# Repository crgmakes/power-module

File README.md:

# Aquarius Power Module

Main power module for Aquarius

# Software 

You will need [KiCad](https://kicad.org) to view and edit this design. Click [here](https://www.kicad.org/download/) to download.

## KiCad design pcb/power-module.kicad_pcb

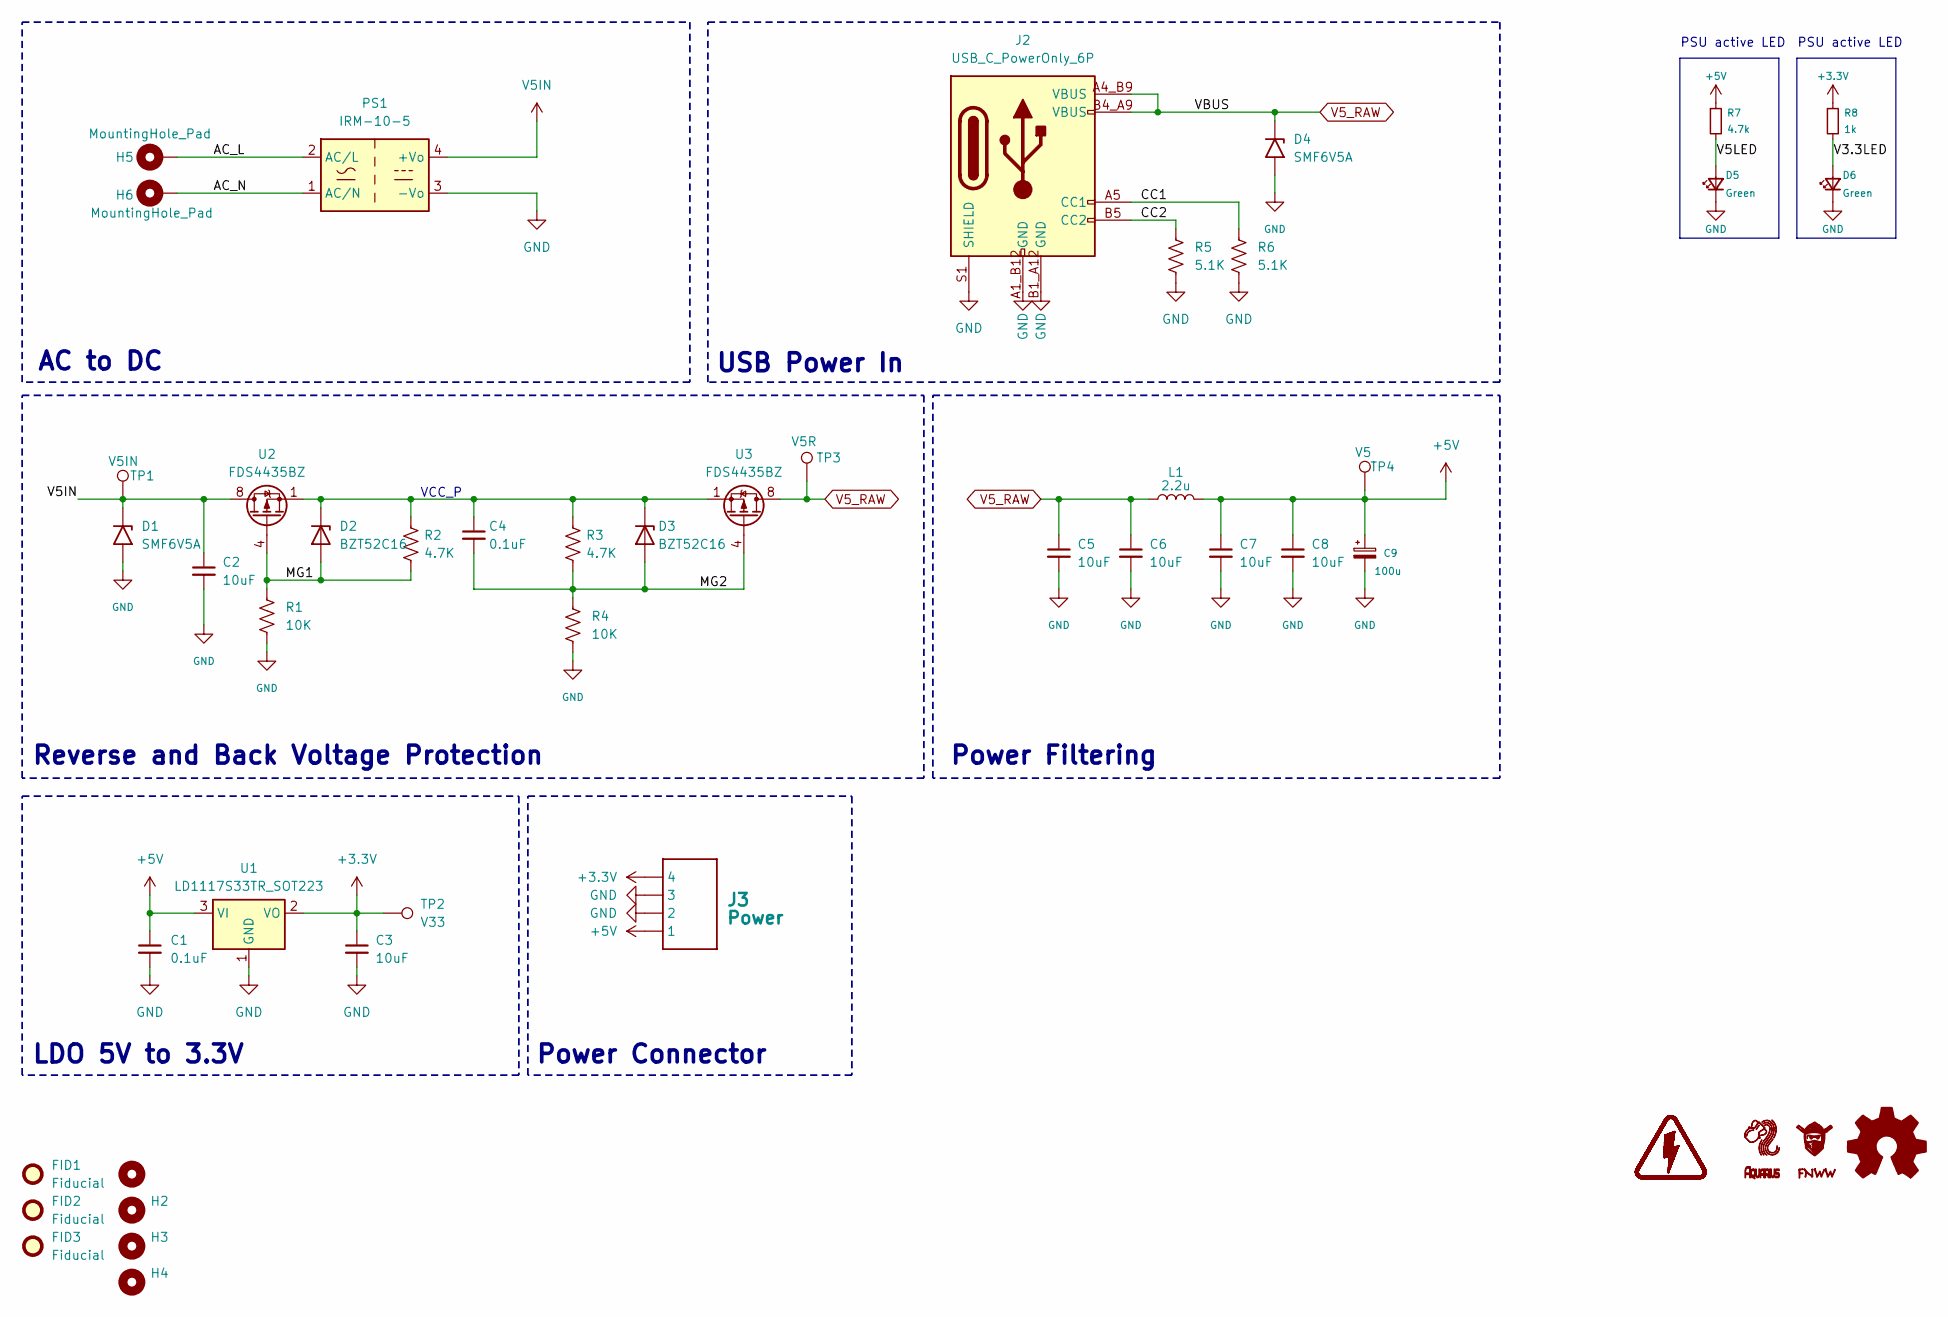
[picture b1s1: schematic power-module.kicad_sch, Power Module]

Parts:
C1, C4: 0.1uF; C_0603_1608Metric; MPN CL10B104KO8NNNC; LCSC C66501
C2, C3, C5, C6, C7, C8: 10uF; C_0603_1608Metric; MPN CL10A106MO8NQNC; LCSC C92487
C9: 100u; CP_Elec_6.3x7.7; JLCPCB C3339
D1, D4: SMF6V5A; D_SOD-123F; MPN SMF6.5A; LCSC C2943842
D2, D3: BZT52C16; D_SOD-123; JLCPCB C216724
D5, D6: Green; LED_0805_2012Metric; LCSC C965815
FID1, FID2, FID3: Fiducial; Fiducial_0.75mm_Mask1.5mm
H1, H2, H3, H4: MountingHole; MountingHole_3.2mm_M3_Pad_Via
H5, H6: MountingHole_Pad; MountingHole_3.2mm_M3_Pad_Via
J2: USB_C_PowerOnly_6P; GCT_USB4105-GF-A
J3: Power; JST_SH_SM04B-SRSS-TB_1x04-1MP_P1.00mm_Horizontal; MPN SM04B-SRSS-TB; LCSC C2763614
L1: 2.2u; L_Sunlord_MWSA0402S; MPN MWSA0402S-2R2MT; JLCPCB C408335
LOGO1: Aquarius Logo 5mm
LOGO2: Aquarius Name 2mmx5mm
LOGO3: FNWW Face 5mm
LOGO4: FNWW Name 2mmx5mm
LOGO5: Logo_Open_Hardware_Small; OSHW-Symbol_6.7x6mm_SilkScreen
PS1: IRM-10-5; Converter_ACDC_MeanWell_IRM-10-xx_THT; LCSC C2857903
R1, R4: 10K; R_0603_1608Metric; MPN FRC0603J103 TS; LCSC_PN C2930027
R2, R3: 4.7K; R_0603_1608Metric; MPN FRC0603J472 TS; LCSC_PN C2907166
R5, R6: 5.1K; R_0603_1608Metric; MPN FRC0603J512 TS; LCSC C2907114
R7: 4.7k; R_0805_2012Metric; Digikey RMCF0805FT10K0CT-ND
R8: 1k; R_0805_2012Metric; Digikey RMCF0805FT10K0CT-ND
S1: HIGH-VOLTAGE-5MM
TP1: V5IN; TestPoint_Pad_D1.0mm
TP2: V33; TestPoint_Pad_D1.0mm
TP3: V5R; TestPoint_Pad_D1.0mm
TP4: V5; TestPoint_Pad_D1.0mm
U1: LD1117S33TR_SOT223; SOT-223-3_TabPin2; MPN LD1117S33TR; LCSC_PN C86781
U2, U3: FDS4435BZ; SO-8_3.9x4.9mm_P1.27mm; JLCPCB C23931

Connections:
+3.3V: C3.1, J3.4, R8.1, TP2.1, U1.2 (VO)
+5V: C1.1, C7.1, C8.1, C9.1, J3.1, L1.2, R7.1, TP4.1, U1.3 (VI)
/AC_L: H5.1, PS1.2 (AC/L)
/AC_N: H6.1, PS1.1 (AC/N)
/CC1: J2.A5 (CC1), R6.1
/CC2: J2.B5 (CC2), R5.1
/MG1: D2.2 (A), R1.1, R2.2, U2.4 (G)
/MG2: C4.2, D3.2 (A), R3.2, R4.1, U3.4 (G)
/V3.3LED: D6.2 (A), R8.2
/V5LED: D5.2 (A), R7.2
GND: C1.2, C2.2, C3.2, C5.2, C6.2, C7.2, C8.2, C9.2, D1.2 (A2), D4.2 (A2), D5.1 (K), D6.1 (K), J2.A1_B12 (GND), J2.B1_A12 (GND), J2.S1 (SHIELD), J3.2, J3.3, PS1.3 (-Vo), R1.2, R4.2, R5.2, R6.2, U1.1 (GND)
unnamed: C4.1, D2.1 (K), D3.1 (K), R2.1, R3.1, U2.1 (S), U2.2 (S), U2.3 (S), U3.1 (S), U3.2 (S), U3.3 (S)
V5IN: C2.1, D1.1 (A1), PS1.4 (+Vo), TP1.1, U2.5 (D), U2.6 (D), U2.7 (D), U2.8 (D)
V5_RAW: C5.1, C6.1, D4.1 (A1), J2.A4_B9 (VBUS), J2.B4_A9 (VBUS), L1.1, TP3.1, U3.5 (D), U3.6 (D), U3.7 (D), U3.8 (D)

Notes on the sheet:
AC to DC
VCC_P
Power Filtering
Reverse and Back Voltage Protection
Power Connector
USB Power In
PSU active LED
LDO 5V to 3.3V

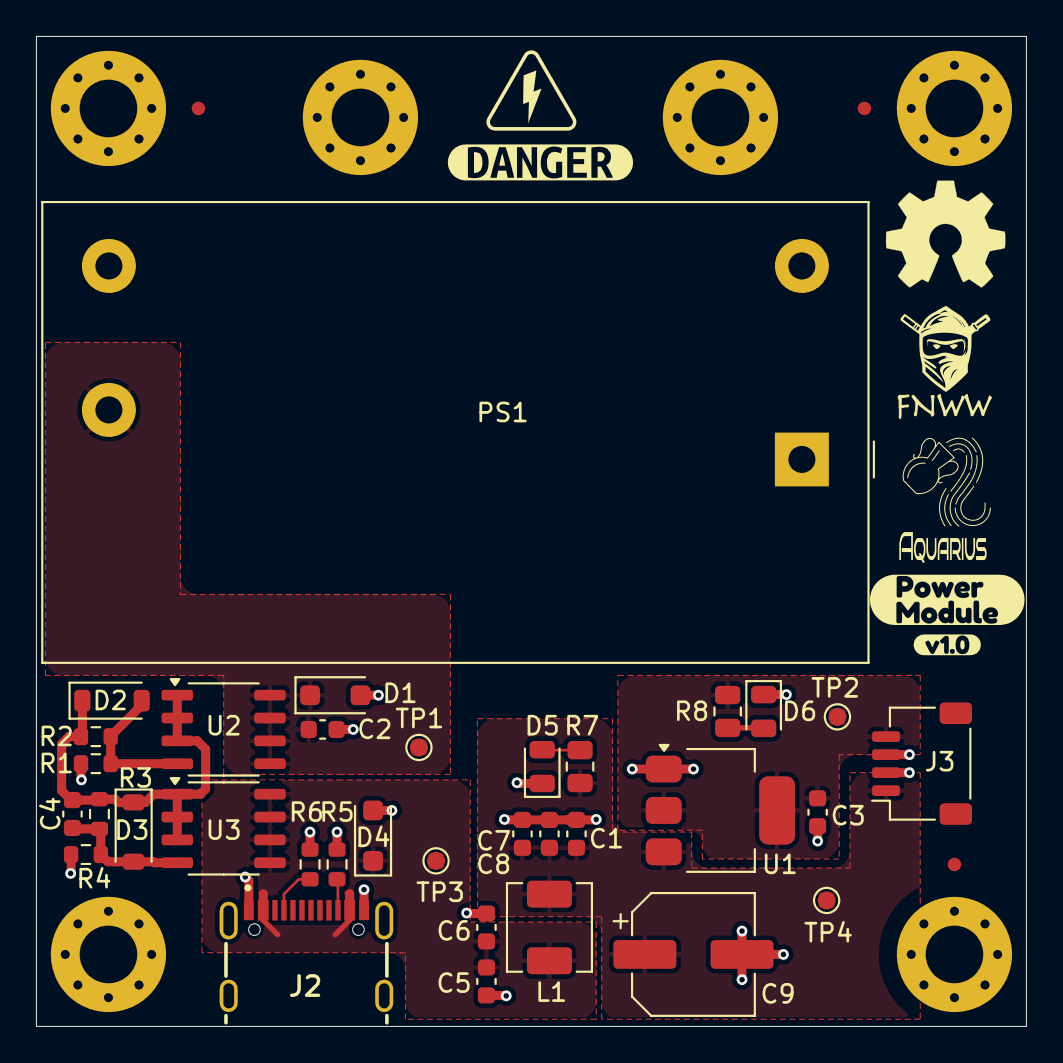
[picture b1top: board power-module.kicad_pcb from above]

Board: 4 copper layers, 55.0 x 55.0 mm, 52 parts (0 on the bottom side), 14 nets.

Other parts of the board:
kibuzzard-67E1D06C: G***; kibuzzard-67E1D06C
kibuzzard-67E31E9F: G***; kibuzzard-67E31E9F
kibuzzard-67E32962: G***; kibuzzard-67E32962

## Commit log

2025-03-22 Update LICENSE
2025-03-25 Initial check in of design
    Updated gitignore.
2025-03-26 Updated readme.
